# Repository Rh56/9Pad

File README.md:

# 9Pad
My custom macro pad! I plan to use this to improve my workflow while doing school work or other tasks on my computer by binding the buttons to different shortcuts. This was first time ever creating a PCB or schematic, so I tried to follow the tutorial while making it my own. I definitely learned a ton. If I did this project again I would want to add an encoder and the OLED display, I was just unsure how I would wire them. Overall, I think I learned a lot and really enjoyed making this project! 

BOM:
- 1x XIAO RP2040
- 9x Cherry MX switches and keycaps
- 1x SK6812 MINI-E
- 1x 3D Printed Case
- 4x M3 Screws

Final Model:

Schematic:

PCB:

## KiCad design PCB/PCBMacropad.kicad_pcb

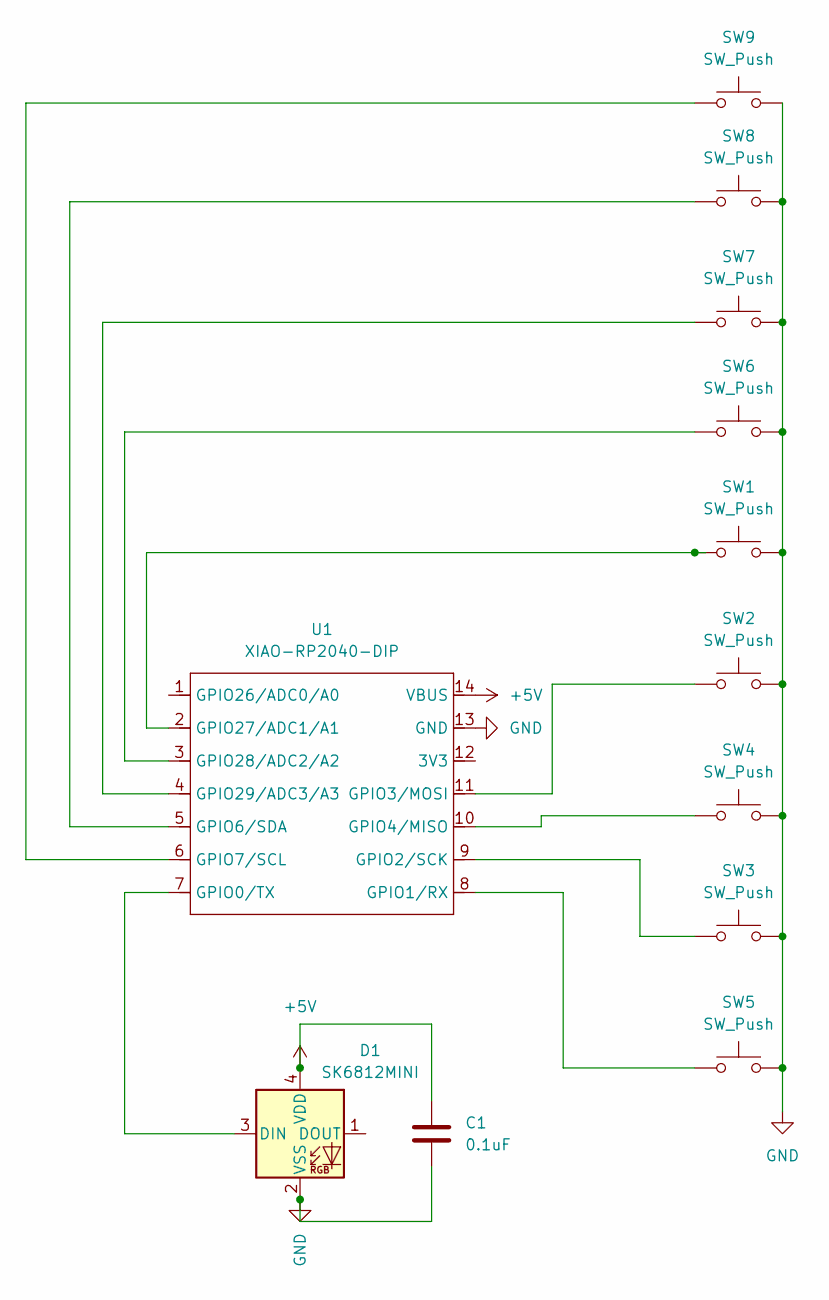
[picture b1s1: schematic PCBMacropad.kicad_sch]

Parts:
C1: 0.1uF; C_Disc_D3.0mm_W1.6mm_P2.50mm
D1: SK6812MINI; LED_SK6812MINI_PLCC4_3.5x3.5mm_P1.75mm
SW1, SW2, SW3, SW4, SW5, SW6, SW7, SW8, SW9: SW_Push; SW_Cherry_MX_1.00u_PCB
U1: XIAO-RP2040-DIP

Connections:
+5V: C1.1, D1.4 (VDD), U1.14 (VBUS)
GND: C1.2, D1.2 (VSS), SW1.2, SW2.2, SW3.2, SW4.2, SW5.2, SW6.2, SW7.2, SW8.2, SW9.2, U1.13 (GND)
unnamed: D1.3 (DIN), U1.7 (GPIO0/TX)
unnamed: SW5.1, U1.8 (GPIO1/RX)
unnamed: SW3.1, U1.9 (GPIO2/SCK)
unnamed: SW2.1, U1.11 (GPIO3/MOSI)
unnamed: SW4.1, U1.10 (GPIO4/MISO)
unnamed: SW8.1, U1.5 (GPIO6/SDA)
unnamed: SW9.1, U1.6 (GPIO7/SCL)
unnamed: SW1.1, U1.2 (GPIO27/ADC1/A1)
unnamed: SW6.1, U1.3 (GPIO28/ADC2/A2)
unnamed: SW7.1, U1.4 (GPIO29/ADC3/A3)

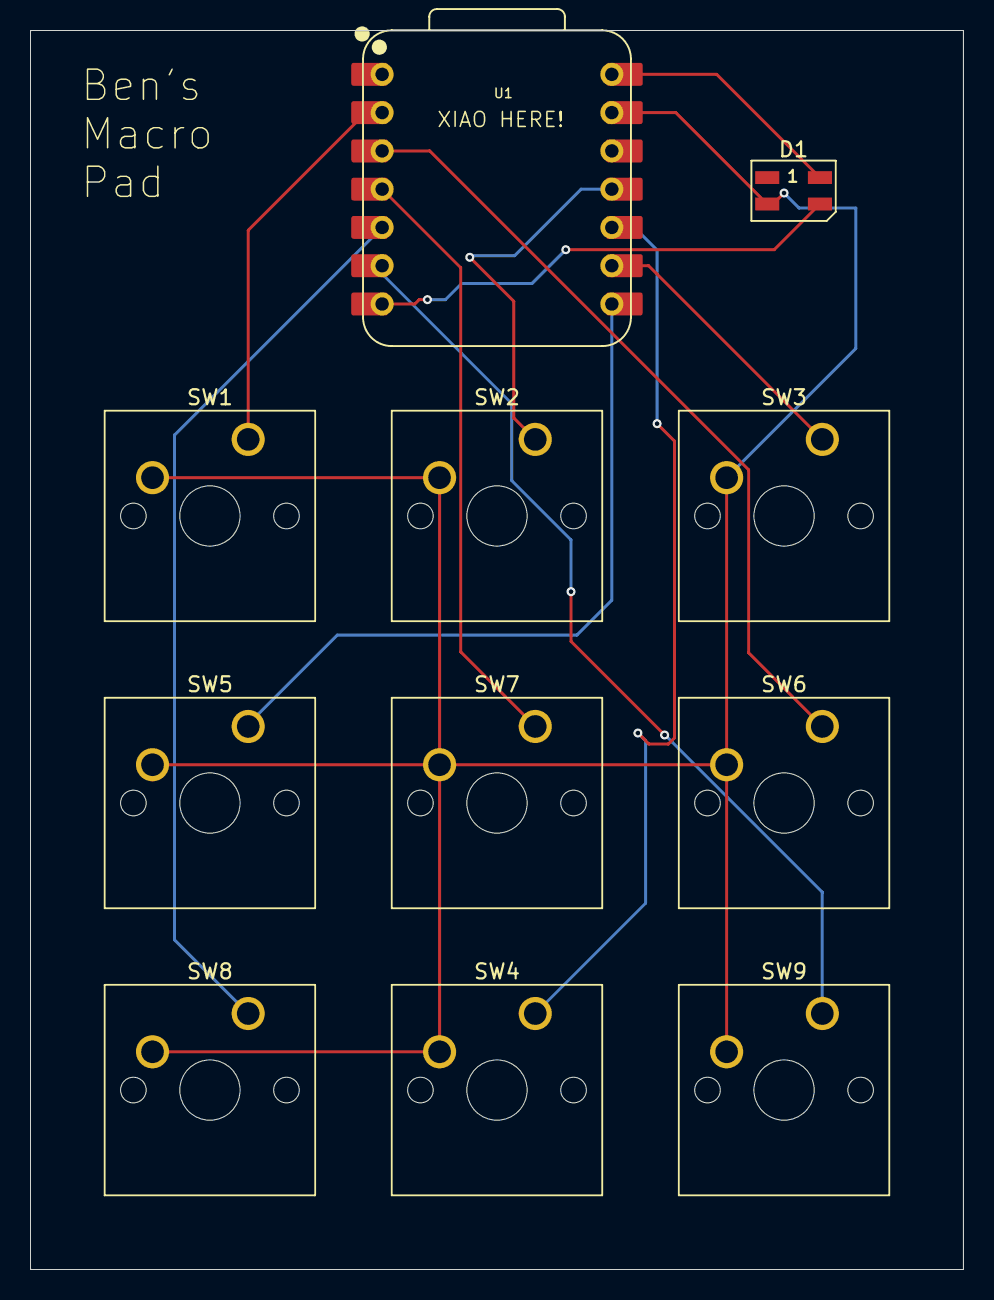
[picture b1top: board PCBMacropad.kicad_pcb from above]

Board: 2 copper layers, 61.9 x 82.2 mm, 11 parts (0 on the bottom side), 12 nets.
